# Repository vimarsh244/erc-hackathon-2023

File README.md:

# ERC Hackathon 2023 submission

### Mechanical

**Design**:

Model files can be found in the `mechanical/` directory or https://a360.co/45wuxL5

**Ansys Analysis**:

Report can be found [here](mechanical/ansys%20analysis/ERC%20HACK%20ANSYS%20MINED.pdf)

### Electronics

Part 1:

[link](https://www.tinkercad.com/things/8tS4cQEKOlx?sharecode=zMyGMb17AG04Dq2QzwaMsAUVSxyepGBn6ncqBjoWyT0)

The differential drive mechanism is a simple 4wd that takes in (linear.x and angular.z) from ROS controller which will accordingly turn the motors.

Part 2:

[link](https://www.tinkercad.com/things/2AzpW1k3oru?sharecode=b2Rh3jejDMBBp6OE0veHATIasINy7RtwA5-mOQYV0L8)

Part 3-6:

[link](https://www.tinkercad.com/things/doNj9fPPetp?sharecode=6bNxCSpgDcdtsFkDNGaQSvCr4-Utx1kQABxrum8ldWc)

Combined all tasks in one circuit.

#### Coil Mechanism

The Sinusoidal wave produced will be connected to a copper coil (basically an inductor). Another copper coil will be receiving the voltage. When connected across a capacitor and near a mine, due to metal eddy currents, there will be changes across voltage in capacitor measured by Arduino.

#### PCBs

The necessary PCBs can be fouond in the `electronics/` directory.

### Automation

**Color Detection**

Cone detection as follows:

**Path Planning**

Example path

Used RRT to create a path, also edited the `obstacle_detection.py` for path to be far away from walls, so that robot doesn't crash with it.

**Controller**

Simple controller for robot to navigate along the planned path. `controller.py`

[demo video of robot moving](misc/final_vid_of_robo_navigating.mp4)

**Others**

run `catkin_make` after cloning in the `~/catkin_ws/src` directory.

Path planner uses RRT to make calculate a path which goes over all points.

`roslaunch robotics_hackathon_automation automation_task.launch`

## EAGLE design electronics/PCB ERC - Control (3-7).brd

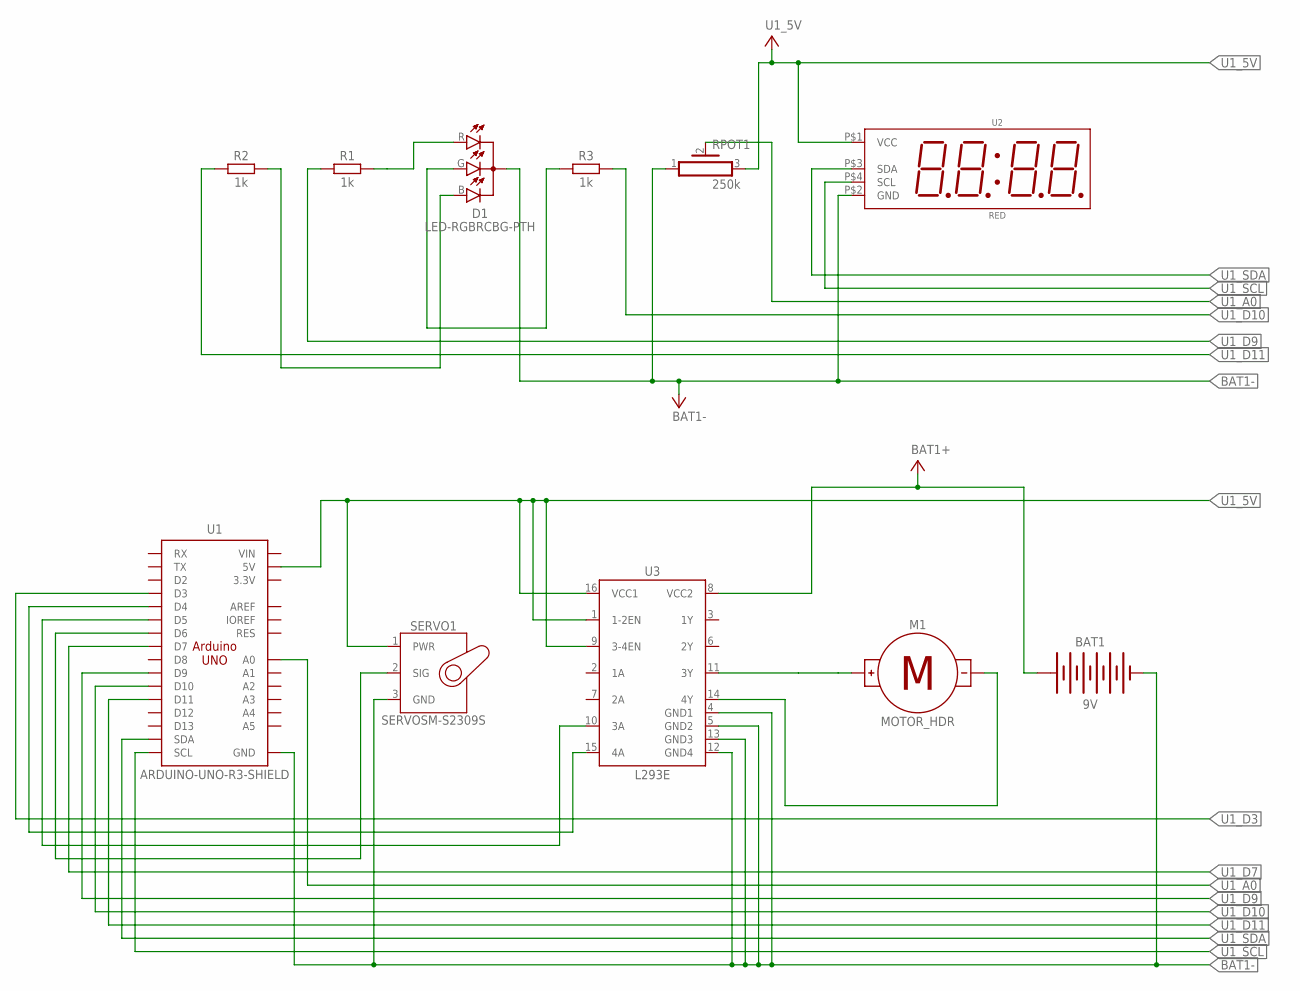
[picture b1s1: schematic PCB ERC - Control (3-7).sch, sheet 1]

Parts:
BAT1: 9V; BATTERY-GENERIC
D1: LED-RGBRCBG-PTH; LED-RGB-5MM
M1: MOTOR_HDR; MOTOR
R1, R2, R3: 1k; RESAD1016W63L850D250B
RPOT1: 250k; HA-06-SM065
SERVO1: SERVOSM-S2309S; SM-S2309S
U1: ARDUINO-UNO-R3-SHIELD
U2: RED; 7SEG-X4-I2C
U3: L293E; DIP762W53P254L1969H508Q16B

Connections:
BAT1+: BAT1.+, U3.8 (VCC2)
BAT1-: BAT1.-, D1.C, RPOT1.1, SERVO1.3 (GND), U1.GND@0 (GND), U1.GND@1 (GND), U1.GND@2 (GND), U2.P$2 (GND), U3.4 (GND1), U3.5 (GND2), U3.12 (GND4), U3.13 (GND3); also elsewhere on the board
D1_B: D1.B, R2.2
D1_G: D1.G, R3.2
D1_R: D1.R, R1.2
M1_+: M1.+, U3.11 (3Y)
M1_-: M1.-, U3.14 (4Y)
U1_5V: RPOT1.3, SERVO1.1 (PWR), U1.5V, U2.P$1 (VCC), U3.1 (1-2EN), U3.9 (3-4EN), U3.16 (VCC1); also elsewhere on the board
U1_A0: RPOT1.2, U1.A0
U1_D3: U1.D3; also elsewhere on the board
U1_D4: U1.D4, U3.15 (4A)
U1_D5: U1.D5, U3.10 (3A)
U1_D6: SERVO1.2 (SIG), U1.D6
U1_D7: U1.D7; also elsewhere on the board
U1_D9: R1.1, U1.D9
U1_D10: R3.1, U1.D10
U1_D11: R2.1, U1.D11
U1_SCL: U1.SCL, U2.P$4 (SCL)
U1_SDA: U1.SDA, U2.P$3 (SDA)

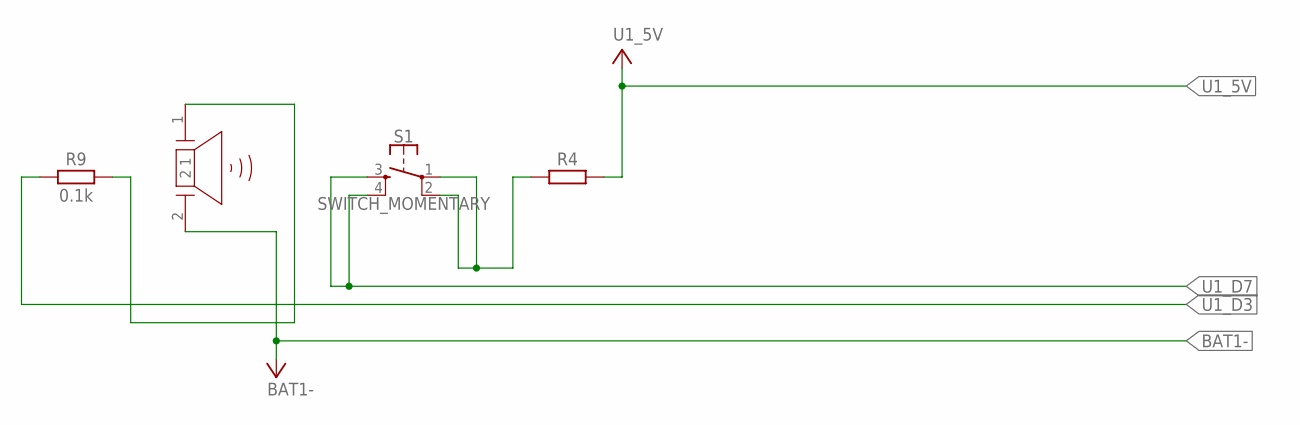
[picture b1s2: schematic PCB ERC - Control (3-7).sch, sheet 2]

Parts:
PIEZO1: PIEZO
R4: RESISTOR_AXIAL-10.16MM-PITCH; RESAD1016W63L850D250B
R9: 0.1k; RESAD1016W63L850D250B
S1: SWITCH_MOMENTARY; SWITCH-MOMENTARY-PTH-6.5MM

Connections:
BAT1-: PIEZO1.2; also elsewhere on the board
PIEZO1_1: PIEZO1.1, R9.2
S1_1: R4.1, S1.1, S1.2
U1_5V: R4.2; also elsewhere on the board
U1_D3: R9.1; also elsewhere on the board
U1_D7: S1.3, S1.4; also elsewhere on the board

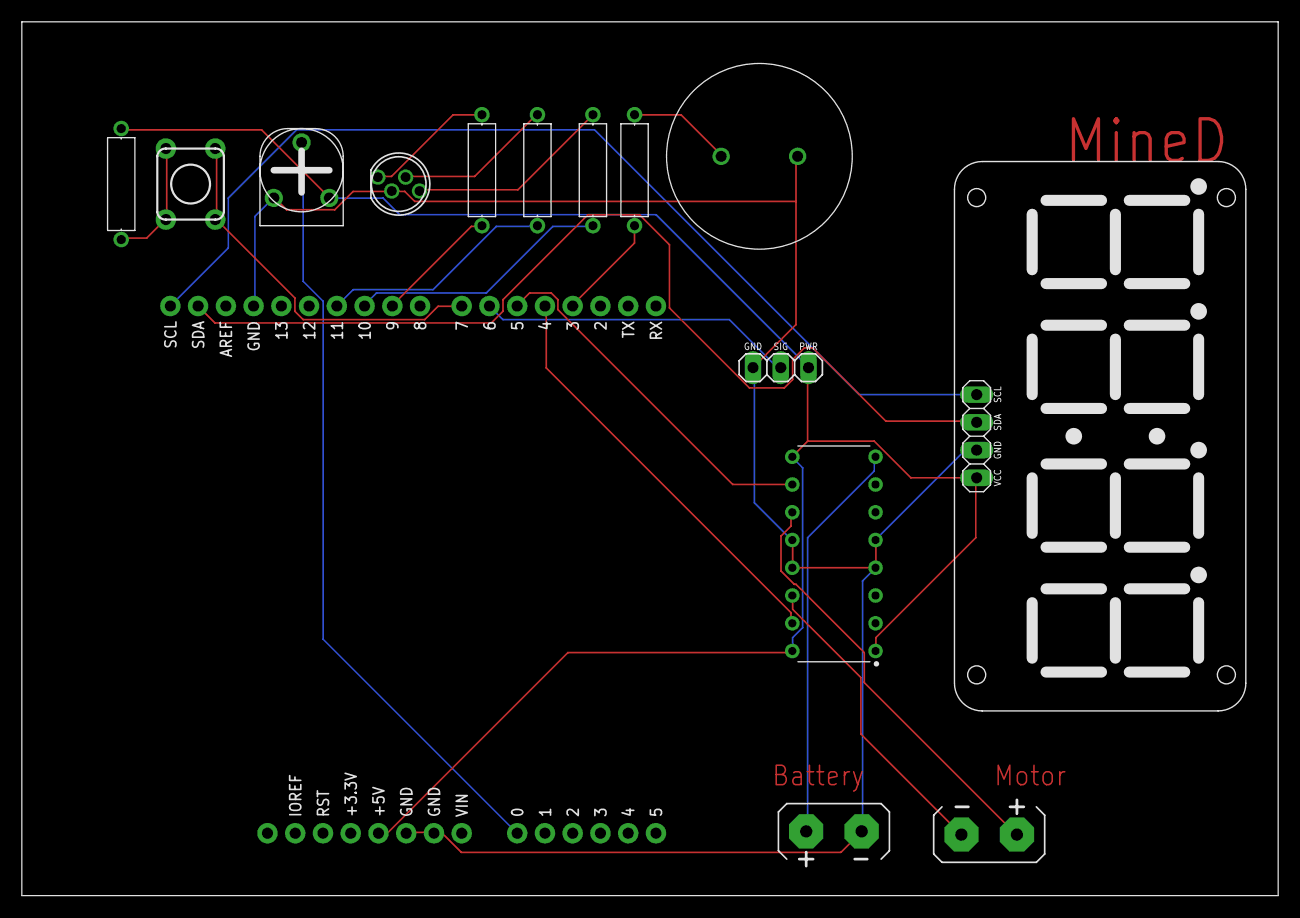
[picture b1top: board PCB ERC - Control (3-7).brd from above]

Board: 2 copper layers, 115.0 x 80.0 mm, 15 parts (0 on the bottom side), 21 nets.

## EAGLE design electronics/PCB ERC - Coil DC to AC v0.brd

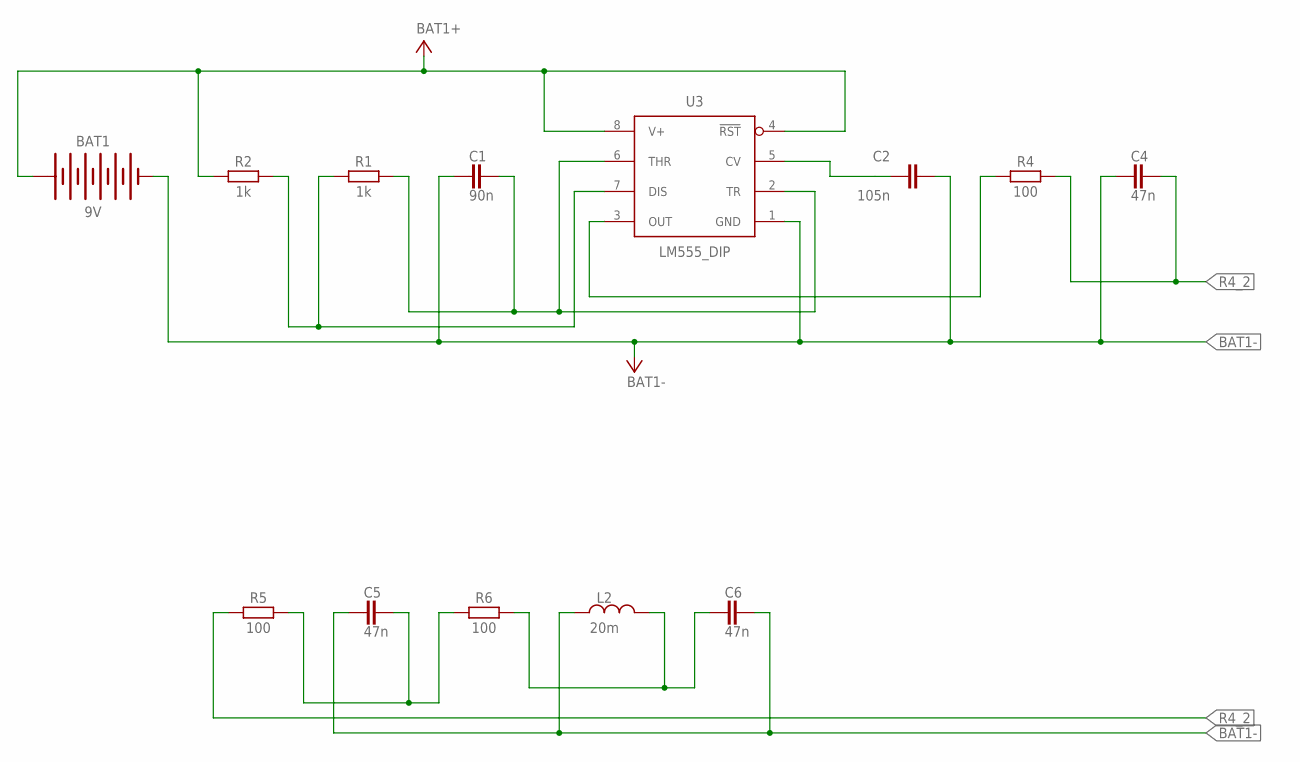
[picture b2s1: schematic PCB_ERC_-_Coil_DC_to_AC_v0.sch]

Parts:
BAT1: 9V; BATTERY-GENERIC
C1: 90n; CAP-THRU-2.54MM
C2: 105n; CAP-THRU-2.54MM
C4, C5, C6: 47n; CAP-THRU-2.54MM
L2: 20m; INDRD2743W50D3810H2616B
R1, R2: 1k; RESAD1016W63L850D250B
R4, R5, R6: 100; RESAD1016W63L850D250B
U3: LM555_DIP; DIP826W53P254L959H508Q8B

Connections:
BAT1+: BAT1.+, R2.2, U3.4 (!RST), U3.8 (V+)
BAT1-: BAT1.-, C1.2, C2.2, C4.2, C5.2, C6.1, L2.1, U3.1 (GND)
R4_2: C4.1, R4.2, R5.1
R5_2: C5.1, R5.2, R6.1
R6_2: C6.2, L2.2, R6.2
U3_CV: C2.1, U3.5 (CV)
U3_DIS: R1.2, R2.1, U3.7 (DIS)
U3_OUT: R4.1, U3.3 (OUT)
U3_THR: C1.1, R1.1, U3.2 (TR), U3.6 (THR)

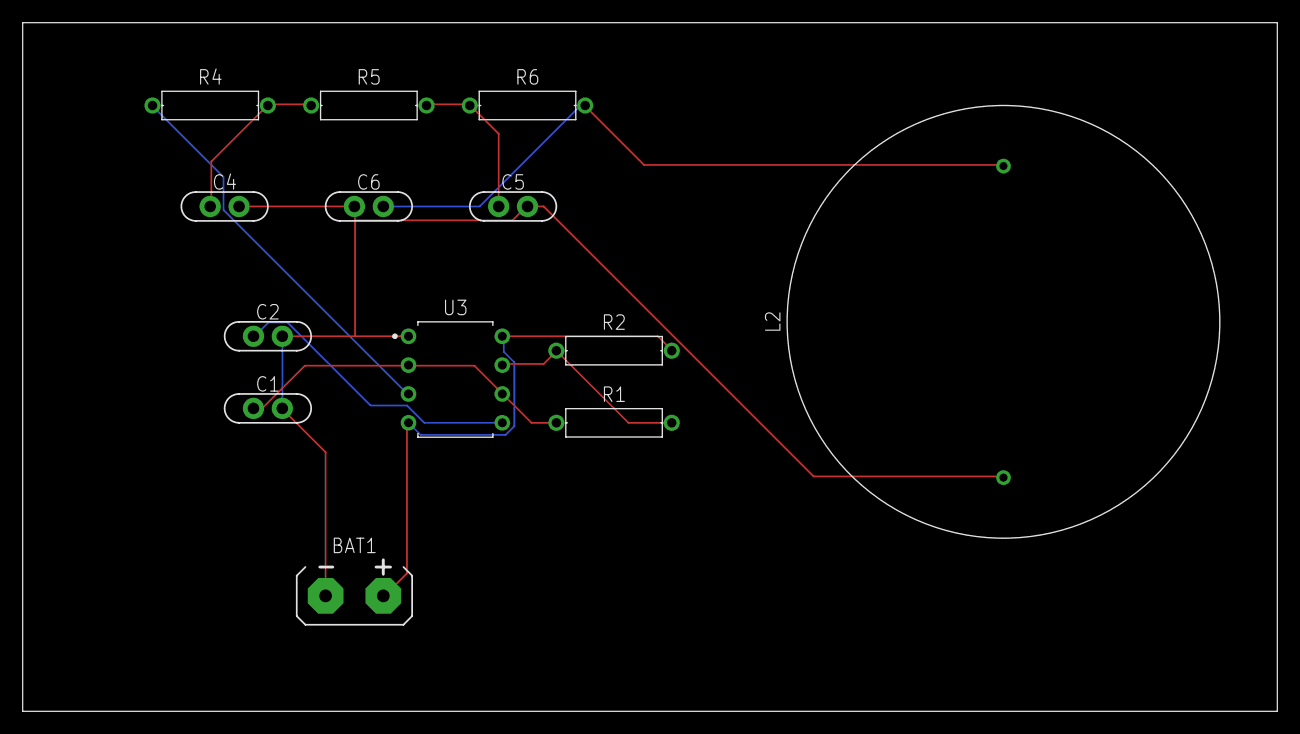
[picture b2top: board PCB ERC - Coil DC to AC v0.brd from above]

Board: 2 copper layers, 110.5 x 60.6 mm, 13 parts (0 on the bottom side), 9 nets.

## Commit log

2023-08-23 few changes, to implement RRT path planning
2023-08-23 path planning done, kind of.. have to test some edge cases
2023-08-23 readme change
2023-08-23 added better visualizer + a good path planning run
2023-08-23 change to add buffer for walls, varna path is ridiculously close
2023-08-23 add buffer and then do run, also pycache fix
2023-08-23 almost done with path planning, this is good imo
2023-08-24 try1 - planner
2023-08-26 all commit timings are messed up, cause NTP didnt work
2023-08-26 now time fixed _ try another controller thing
2023-08-26 yay it works, goes from point a to b to a ...
2023-08-27 aint workin
2023-08-27 added an array of points which T3 follows but it doesnt work, due to overshoot and all, so will have to implement good pid controll
2023-08-27 Added color detection.
2023-08-27 control script first test
2023-08-27 fix, it rotated in CW only
2023-08-27 control thing workssss
2023-08-27 entirely went around maze perfectly no pid control though, just simple instructions
2023-08-27 stupid try to improve path planning, as currently moves very robotic
2023-08-27 new run, so much better path
2023-08-27 huaa
2023-08-27 added few electronics tasks done
2023-08-27 added custom message for publishing coordinates took far to long, dependencies issues
2023-08-28 custom message not workin :(
2023-08-28 nested messages try
2023-08-28 controller kinda works but not exactly
2023-08-28 final touches to add
2023-08-28 add docs
2023-08-29 update electronics
2023-08-29 my approach so far was that path planning plans and publishes it as checkpoints, which then controller loads and does things that isn't working so now changing it
2023-08-29 low battery commit
2023-08-30 added electronics
2023-08-30 update report
2023-08-30 regex ftw
2023-08-30 it works!
2023-08-30 add other scripts to launch file
2023-08-30 cleaning code + finalizing
2023-08-30 minute fixes
